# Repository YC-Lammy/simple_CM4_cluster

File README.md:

# simple_CM4_cluster
A simple compute module 4 cluster in a 120x120x60mm form-factor cabable of up to 7 pi.   

Each pi can work alone as a 78x58mm SBC.

Ports(per pi): 4 usb2.0, usb-c OTG, PCIE, 2 micro HDMI, CSI, DSI, micro SD and headers

The last six pin on the standard 40 way header has been removed on the board, include GPIO 16,19,20,21,26 and GND

SPI, I2C, UART are not affected, a standard HAT device can still be used.

The main board is powered by +12v through barrel jack or 4/8 pin PSU power. When the pi is alone, it could be powered through USB-A or pin headers

Two space left for EEPROM on the main PCB can be left open if custom program for the RTL8370 is not required. SW2 is a restart switch of RTL8370.

Requirement: kiCad version 5.99 or above

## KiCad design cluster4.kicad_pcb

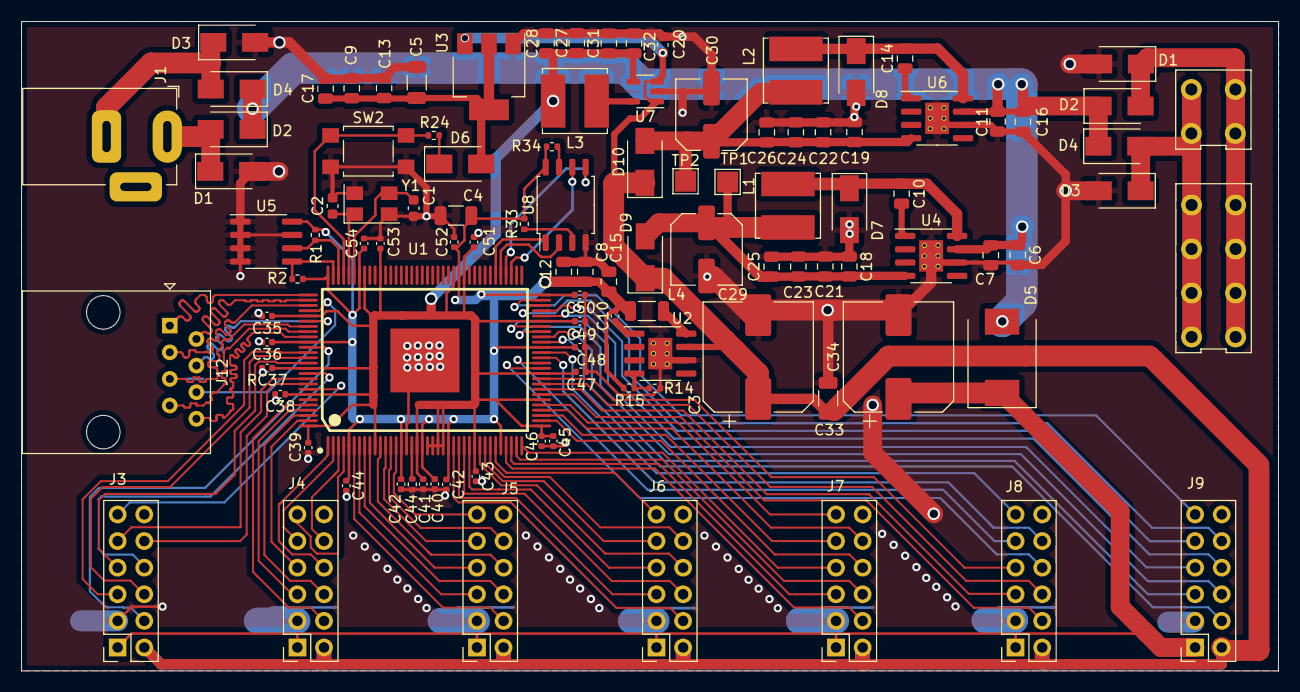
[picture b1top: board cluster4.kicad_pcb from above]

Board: 2 copper layers, 120.0 x 62.0 mm, 105 parts (0 on the bottom side), 93 nets.

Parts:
C1, C2: pf; C_0603_1608Metric
C3, C34: 470uf; CP_Elec_10x10
C4, C5: 100uf; C_1206_3216Metric
C6, C7, C11, C16, C18, C19, C21, C22, C23, C24, C25, C26: 10u; C_0805_2012Metric
C8, C9: 22uf; C_0805_2012Metric
C10: 10n; C_0402_1005Metric
C10#2, C14: 100n; C_0805_2012Metric
C12, C13, C15, C17, C27, C28, C31, C32: 10uf; C_0805_2012Metric
C20: 4.7uf; C_0603_1608Metric
C29, C30: 100uf; C_Elec_6.3x7.7
C33: 470uf; C_1206_3216Metric
C35, C36, C38, C39, C40, C41, C42, C42#2, C43, C44, C45, C46, C47, C48, C49, C50, C51, C52, C53, C54: 0.1uf; C_0402_1005Metric
C44#2: 2.49k; R_0402_1005Metric
D1, D1#2, D2, D2#2, D3, D3#2, D4, D4#2, D6, D9, D10: D; D_SMA
D5: D_SMC
D7, D8: 1n5824; D_SMA
J1: Barrel_Jack; BarrelJack_Horizontal
J2, J2#2: Conn_02x12_Top_Bottom; 5557_connector
J3, J4, J5, J6, J7, J8, J9: Conn_01x11_Female; PinSocket_2x06_P2.54mm_Vertical
J12: RJ45; RJ45_Amphenol_54602-x08_Horizontal
L1, L2: 22uh; L_Bourns_SRN6045TA
L3: 1uh; L_Bourns_SRN6045TA
L4: 6.8uh; L_1206_3216Metric
R1, R2, R15: 4.7k; R_0402_1005Metric
R14: 3k; R_0402_1005Metric
R24: 10k; R_0402_1005Metric
R33, R34: 1k; R_0402_1005Metric
RC37: 0.1uf; C_0402_1005Metric
SW2: SW_Push; SW_SPST_TL3305A
TP1, TP2: TestPoint; TestPoint_Pad_2.0x2.0mm
U1: RTL8370N; RTL8370
U2: LM22676-ADJ; SOIC-8-1EP_3.9x4.9mm_P1.27mm_EP2.29x3mm_ThermalVias
U3: AMS1117-3.3; SOT-223-3_TabPin2
U4, U6: LM22676-5.0; SOIC-8-1EP_3.9x4.9mm_P1.27mm_EP2.29x3mm_ThermalVias
U5: M24C02-FMN; SOIC-8_3.9x4.9mm_P1.27mm
U7: ADP2108AUJ-1.0; TSOT-23-5
U8: W25Q128JVS; SOIC-8_5.23x5.23mm_P1.27mm
Y1: 25Mhz; Crystal_SMD_5032-4Pin_5.0x3.2mm

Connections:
/+5v: C3.1, C20.1, C33.1, D9.1 (K), D10.1 (K), J3.2, J4.2, J5.2, J6.2, J7.2, J8.2, J9.2, U2.7, U3.3 (VI), U7.1 (Vin), U7.3 (EN)
/+12v: C34.1, D5.1, J3.1, J4.1, J5.1, J6.1, J7.1, J8.1, J9.1
/P0_AN: J12.2, U1.104 (P0MDIAN)
/P0_AP: J12.1, U1.103 (P0MDIAP)
/P0_BN: J12.6, U1.106 (P0MDIBN)
/P0_BP: J12.3, U1.105 (P0MDIBP)
/P0_CN: J12.5, U1.109 (P0MDICN)
/P0_CP: J12.4, U1.108 (P0MDICP)
/P0_DN: J12.8, U1.111 (P0MDIDN)
/P0_DP: J12.7, U1.110 (P0MDIDP)
/P1_AN: J3.5, U1.114 (P1MDIAN)
/P1_AP: J3.4, U1.113 (P1MDIAP)
/P1_BN: J3.7, U1.116 (P1MDIBN)
/P1_BP: J3.6, U1.115 (P1MDIBP)
/P1_CN: J3.9, U1.119 (P1MDICN)
/P1_CP: J3.8, U1.118 (P1MDICP)
/P1_DN: J3.11, U1.121 (P1MDIDN)
/P1_DP: J3.10, U1.120 (P1MDIDP)
/P2_AN: J4.5, U1.125 (P2MDIAN)
/P2_AP: J4.4, U1.124 (P2MDIAP)
/P2_BN: J4.7, U1.127 (P2MDIBN)
/P2_BP: J4.6, U1.126 (P2MDIBP)
/P2_CN: J4.9, U1.2 (P2MDICN)
/P2_CP: J4.8, U1.1 (P2MDICP)
/P2_DN: J4.11, U1.4 (P2MDIDN)
/P2_DP: J4.10, U1.3 (P2MDIDP)
/P3_AN: J5.5, U1.7 (P3MDIAN)
/P3_AP: J5.4, U1.6 (P3MDIAP)
/P3_BN: J5.7, U1.9 (P3MDIBN)
/P3_BP: J5.6, U1.8 (P3MDIBP)
/P3_CN: J5.9, U1.12 (P3MDICN)
/P3_CP: J5.8, U1.11 (P3MDICP)
/P3_DN: J5.11, U1.14 (P3MDIDN)
/P3_DP: J5.10, U1.13 (P3MDIDP)
/P4_AN: J6.5, U1.26 (P4MDIAN)
/P4_AP: J6.4, U1.25 (P4MDIAP)
/P4_BN: J6.7, U1.28 (P4MDIBN)
/P4_BP: J6.6, U1.27 (P4MDIBP)
/P4_CN: J6.9, U1.31 (P4MDICN)
/P4_CP: J6.8, U1.30 (P4MDICP)
/P4_DN: J6.11, U1.33 (P4MDIDN)
/P4_DP: J6.10, U1.32 (P4MDIDP)
/P5_AN: J7.5, U1.36 (P5MDIAN)
/P5_AP: J7.4, U1.35 (P5MDIAP)
/P5_BN: J7.7, U1.38 (P5MDIBN)
/P5_BP: J7.6, U1.37 (P5MDIBP)
/P5_CN: J7.9, U1.41 (P5MDICN)
/P5_CP: J7.8, U1.40 (P5MDICP)
/P5_DN: J7.11, U1.43 (P5MDIDN)
/P5_DP: J7.10, U1.42 (P5MDIDP)
/P6_AN: J8.5, U1.46 (P6MDIAN)
/P6_AP: J8.4, U1.45 (P6MDIAP)
/P6_BN: J8.7, U1.48 (P6MDIBN)
/P6_BP: J8.6, U1.47 (P6MDIBP)
/P6_CN: J8.9, U1.51 (P6MDICN)
/P6_CP: J8.8, U1.50 (P6MDICP)
/P6_DN: J8.11, U1.53 (P6MDIDN)
/P6_DP: J8.10, U1.52 (P6MDIDP)
/P7_AN: J9.5, U1.56 (P7MDIAN)
/P7_AP: J9.4, U1.55 (P7MDIAP)
/P7_BN: J9.7, U1.58 (P7MDIBN)
/P7_BP: J9.6, U1.57 (P7MDIBP)
/P7_CN: J9.9, U1.61 (P7MDICN)
/P7_CP: J9.8, U1.60 (P7MDICP)
/P7_DN: J9.11, U1.63 (P7MDIDN)
/P7_DP: J9.10, U1.62 (P7MDIDP)
/switch/+1v: C27.1, C28.1, C31.1, C32.1, C35.1, C38.1, C39.1, C41.1, C43.1, C45.1, C46.1, C47.1, C49.1, C51.1, C53.1, L3.2, RC37.1, U1.10 (AVDDL), U1.18 (AVDDL), U1.20 (DVDDL), U1.21 (DVDDL), U1.22 (DVDDL), U1.23 (DVDDL), U1.29 (AVDDL), U1.39 (AVDDL), U1.44 (PLLVDDL1), U1.49 (AVDDL), U1.59 (AVDDL), U1.76 (DVDDL), U1.78 (DVDDL), U1.92 (DVDDL), U1.95 (DVDDL), U1.107 (AVDDL), U1.117 (AVDDL), U1.122 (PLLVDDL0), U1.128 (AVDDL), U7.4 (FB)
/switch/SCK: R1.1, U1.100 (SCK/MDC), U5.6 (SCL)
/switch/SDA: R2.1, U1.101 (SDA/MDIO), U5.5 (SDA)
/switch/SPI_CLK: U1.67 (P7LED2), U8.6 (CLK)
/switch/SPI_CS: U1.70 (P6LED2), U8.1 (~CS)
/switch/SPI_D0: U1.69 (P7LED1), U8.2 (DO(IO1))
/switch/SPI_D1: U1.68 (P7LED0), U8.5 (DI(IO0))
/switch/nRESET: R24.2, SW2.1, U1.99 (nRESET)
<NO NET>: C4.1, C8.1, C10.2, C12.1, C15.1, C36.1, C40.1, C42.1, C42#2.1, C44.1, C48.1, C50.1, C52.1, C54.1, L4.1, R1.2, R2.2, R15.1, R33.2, R34.2, U1.5 (AVDDH), U1.15 (AVDDH), U1.19 (AVDDH), U1.24 (AVDDH), U1.34 (AVDDH), U1.54 (AVDDH), U1.64 (AVDDH), U1.77 (DVDDIO), U1.96 (AVDDH), U1.102 (AVDDH), U1.112 (AVDDH), U5.8 (VCC), U8.8 (VCC)
GND: C1.2, C2.2, C3.2, C4.2, C5.2, C6.2, C7.2, C8.2, C9.2, C11.2, C12.2, C13.2, C15.2, C16.2, C17.2, C18.2, C19.2, C20.2, C21.2, C22.2, C23.2, C24.2, C25.2, C26.2, C27.2, C28.2, C29.2, C30.2, C31.2, C32.2, C33.2, C34.2, C35.2, C36.2, C38.2, C39.2, C40.2, C41.2, C42.2, C42#2.2, C43.2, C44.2, C44#2.1, C45.2, C46.2, C47.2, C48.2, C49.2, C50.2, C51.2, C52.2, C53.2, C54.2, D1.2 (A), D1#2.2 (A), D3.2 (A), D3#2.2 (A), D7.2 (A), D8.2 (A), J3.3, J4.3, J5.3, J6.3, J7.3, J8.3, J9.3, R14.2, RC37.2, SW2.2, U1.16 (AGND), U1.129, U2.6, U2.9, U3.1 (GND), U4.6, U4.9, U5.1 (E0), U5.2 (E1), U5.3 (E2), U5.4 (VSS), U5.7 (~WC), U6.6, U6.9, U7.2 (GND), U8.4 (GND), Y1.2, Y1.4
unnamed: C1.1, U1.97 (XTAL0), Y1.3
unnamed: C2.1, U1.98 (XTAL1), Y1.1
unnamed: C6.1, C7.1, C11.1, C16.1, D2.1 (K), D2#2.1 (K), D4.1 (K), D4#2.1 (K), D5.2, U4.7, U6.7
unnamed: C5.1, C9.1, C13.1, C17.1, D6.2 (A), U3.2 (VO)
unnamed: C18.1, C21.1, C23.1, C25.1, C29.1, D9.2 (A), L1.2, TP1.1, U4.4 (FB)
unnamed: C19.1, C22.1, C24.1, C26.1, C30.1, D10.2 (A), L2.2, TP2.1, U6.4 (FB)
unnamed: D1#2.1 (K), D2#2.2 (A), J1.1
unnamed: D3#2.1 (K), D4#2.2 (A), J1.2
unnamed: D6.1 (K), R24.1
unnamed: C10#2.1, D7.1 (K), L1.1, U4.8
unnamed: C14.2, D8.1 (K), L2.1, U6.8
unnamed: D1.1 (K), D2.2 (A), J2.1 (Pin_2), J2#2.1 (Pin_2)
unnamed: D3.1 (K), D4.2 (A), J2.2 (Pin_13), J2#2.2 (Pin_13)
unnamed: L3.1, U7.5 (SW)
unnamed: C44#2.2, U1.17 (MDIREF)
unnamed: R33.1, U8.3 (IO2)
unnamed: R34.1, U8.7 (IO3)

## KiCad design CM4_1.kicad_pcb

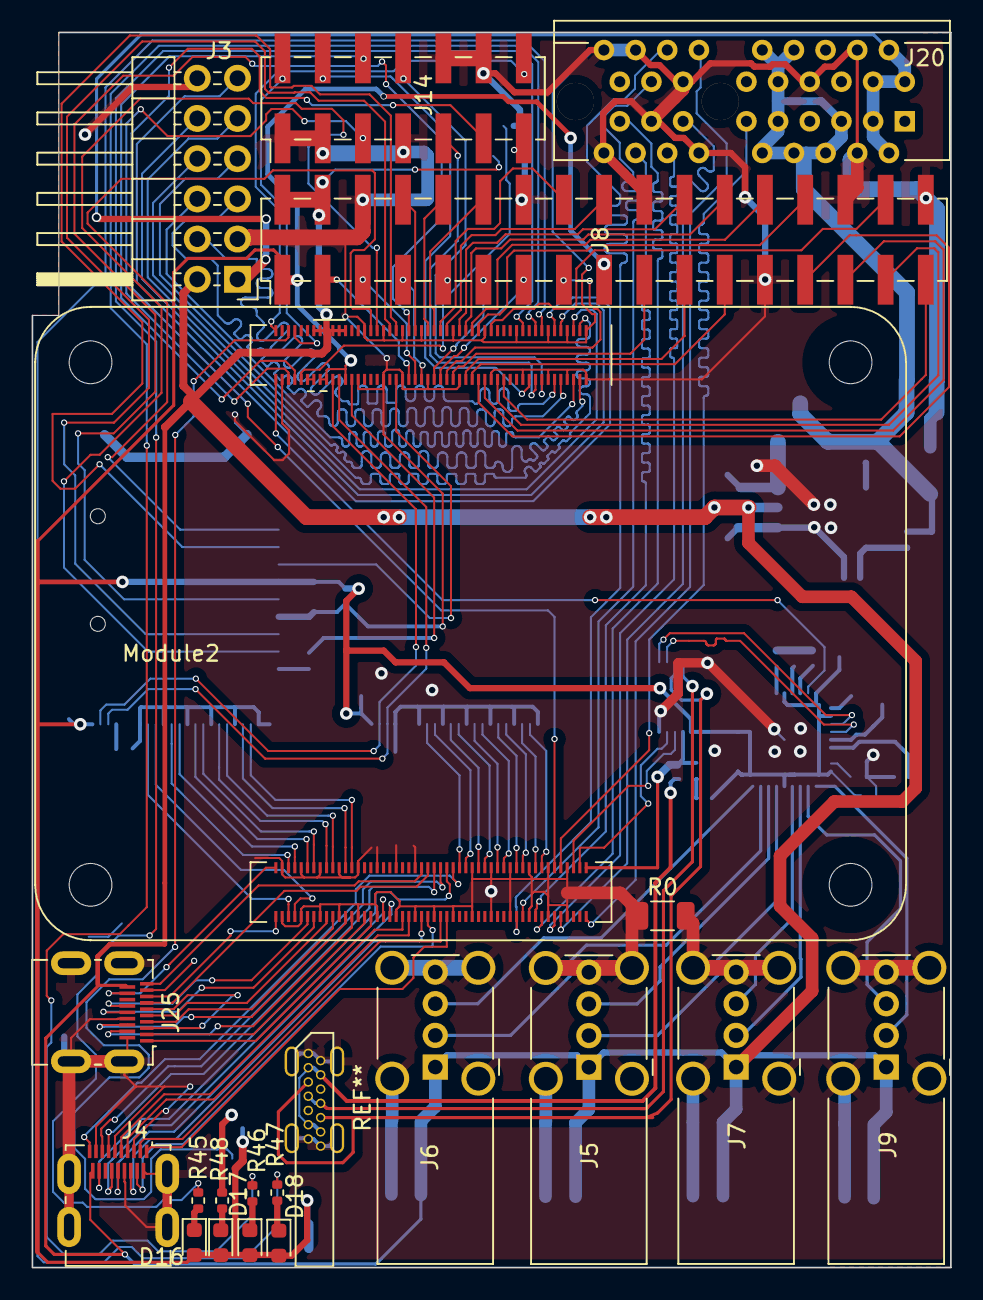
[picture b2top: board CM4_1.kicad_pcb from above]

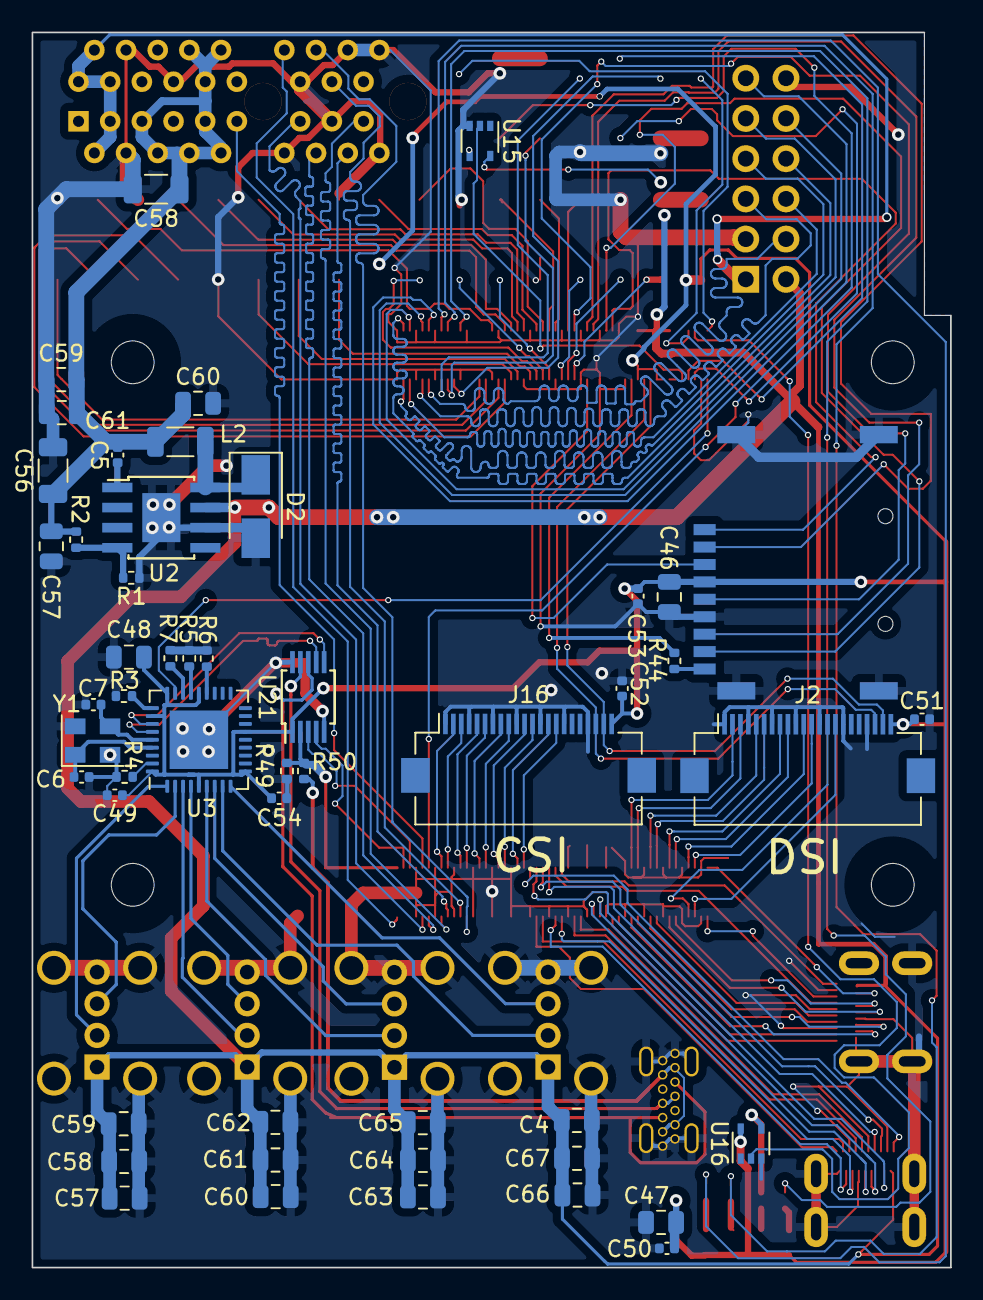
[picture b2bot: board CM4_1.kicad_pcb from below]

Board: 2 copper layers, 58.0 x 78.0 mm, 71 parts (51 on the bottom side), 142 nets.

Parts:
C4, C59, C62, C65: 22uf; C_0805_2012Metric
C5: 10nf; C_0402_1005Metric
C6, C7: 27pF; C_0402_1005Metric
C46, C47, C48, C57, C57#2, C58, C59#2, C60, C60#2, C61, C61#2, C63, C64, C66, C67: 10u; C_0805_2012Metric
C49, C50, C51, C52, C53, C54: 100n; C_0402_1005Metric
C56, C58#2: 100uf; C_1206_3216Metric
D2: SS36; D_SMA
D16: LED Green; LED_0603_1608Metric
D17: LED yellow; LED_0603_1608Metric
D18: LED green; LED_0603_1608Metric
D20: LED Red; LED_0603_1608Metric
J2, J16: Conn_01x22_Female; Hirose_FH12-22S-0.5SH_1x22-1MP_P0.50mm_Horizontal
J3: Conn_01x10_Female; PinHeader_2x06_P2.54mm_Horizontal
J4, J25: 690-019-298-412; HDMI_Micro-D_Molex_46765-1x01
J5, J6, J7, J9: USB_A; USB_A_Wuerth_614004134726_Horizontal
J8: THD-20-R; PinHeader_2x17_P2.54mm_Vertical_SMD
J13: Micro_SD_Card_Det; SD_slot
J14: Conn_02x07_Odd_Even; PinHeader_2x07_P2.54mm_Vertical_SMD
J20: 10018783-11200TLF; PCIex1-36
L2: 6.8uh; L_1206_3216Metric
Module2: ComputeModule4; Raspberry-Pi-4-Compute-Module
R0: 0R; R_1206_3216Metric
R1: 3k; R_0402_1005Metric
R2: 4.7k; R_0402_1005Metric
R3, R5, R6, R7: 36K 1%; R_0402_1005Metric
R4: 12K 1%; R_0402_1005Metric
R44: nf; R_0402_1005Metric
R45, R48: 1k; R_0402_1005Metric
R46, R47: 470R; R_0402_1005Metric
R49, R50: 2.2K 1%; R_0402_1005Metric
U2: LM22676MR-ADJ; TI_SO-PowerPAD-8
U3: USB2514B-I/M2; QFN-36-1EP_6x6mm_P0.5mm_EP3.7x3.7mm
U15, U16: 74LVC1G07SE-7; SOT-353_SC-70-5
U21: FSUSB42MUX; MSOP-10_3x3mm_P0.5mm
Y1: 24MHz; Crystal_SMD_EuroQuartz_MT-4Pin_3.2x2.5mm

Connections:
/+1.8v: Module2.88 (+1.8v_(Output)), Module2.90 (+1.8v_(Output))
/+3.3v: C46.1, C47.1, C48.1, C49.1, C50.1, C51.1, C52.1, C53.1, C54.1, D16.2 (A), D17.2 (A), D18.2 (A), D20.2 (A), J2.22, J8.1, J8.17, J13.4 (VDD), J16.22, Module2.78 (GPIO_VREF(1.8v/3.3v_Input)), Module2.84 (+3.3v_(Output)), Module2.86 (+3.3v_(Output)), U3.5 (VDDA33), U3.10 (VDDA33), U3.15 (VDD33), U3.23 (VDD33), U3.27 (VBUS_DET), U3.29 (VDDA33), U3.36 (VDDA33), U16.5 (VCC), U21.1 (VCC)
/+5v: C4.1, C57#2.2, C58.2, C59.1, C60#2.2, C61.2, C62.1, C63.2, C64.2, C65.1, C66.2, C67.2, J3.2, J4.18 (+5V), J5.1 (VBUS), J6.1 (VBUS), J7.1 (VBUS), J8.2, J8.4, J9.1 (VBUS), J25.18 (+5V), Module2.77 (+5v_(Input)), Module2.79 (+5v_(Input)), Module2.81 (+5v_(Input)), Module2.83 (+5v_(Input)), Module2.85 (+5v_(Input)), Module2.87 (+5v_(Input)), U2.7 (VIN), U15.5 (VCC)
/+12v: J3.1, J20.A2 (+12V), J20.A3 (+12V), J20.B1 (+12v), J20.B2 (+12v), J20.B3 (+12v)
/AIN0: J14.5, Module2.96 (AnalogIP0)
/AIN1: J14.6, Module2.94 (AnalogIP1)
/CAM1_C_N: J16.8, Module2.127 (CAM1_C_N)
/CAM1_C_P: J16.9, Module2.129 (CAM1_C_P)
/CAM1_D0_N: J16.2, Module2.115 (CAM1_D0_N)
/CAM1_D0_P: J16.3, Module2.117 (CAM1_D0_P)
/CAM1_D1_N: J16.5, Module2.121 (CAM1_D1_N)
/CAM1_D1_P: J16.6, Module2.123 (CAM1_D1_P)
/CAM1_D2_N: J16.11, Module2.133 (CAM1_D2_N)
/CAM1_D2_P: J16.12, Module2.135 (CAM1_D2_P)
/CAM1_D3_N: J16.14, Module2.139 (CAM1_D3_N)
/CAM1_D3_P: J16.15, Module2.141 (CAM1_D3_P)
/DSI1_C_N: J2.8, Module2.187 (DSI1_C_N)
/DSI1_C_P: J2.9, Module2.189 (DSI1_C_P)
/DSI1_D0_N: J2.2, Module2.175 (DSI1_D0_N)
/DSI1_D0_P: J2.3, Module2.177 (DSI1_D0_P)
/DSI1_D1_N: J2.5, Module2.181 (DSI1_D1_N)
/DSI1_D1_P: J2.6, Module2.183 (DSI1_D1_P)
/DSI1_D2_N: J2.11, Module2.193 (DSI1_D2_N)
/DSI1_D2_P: J2.12, Module2.195 (DSI1_D2_P)
/DSI1_D3_N: J2.14, Module2.194 (DSI1_D3_N)
/DSI1_D3_P: J2.15, Module2.196 (DSI1_D3_P)
/EEPROM_nWP: J14.4, Module2.20 (EEPROM_nWP)
/ETH_LEDG: Module2.15 (Ethernet_nLED3(3.3v)), R47.2
/ETH_LEDY: Module2.17 (Ethernet_nLED2(3.3v)), R46.2
/GLOBAL_EN: J14.14, Module2.99 (Global_EN)
/GPIO2: J8.3, Module2.58 (GPIO2)
/GPIO3: J8.5, Module2.56 (GPIO3)
/GPIO4: J8.7, Module2.54 (GPIO4)
/GPIO5: J8.29, Module2.34 (GPIO5)
/GPIO6: J8.31, Module2.30 (GPIO6)
/GPIO7: J8.26, Module2.37 (GPIO7)
/GPIO8: J8.24, Module2.39 (GPIO8)
/GPIO9: J8.21, Module2.40 (GPIO9)
/GPIO10: J8.19, Module2.44 (GPIO10)
/GPIO11: J8.23, Module2.38 (GPIO11)
/GPIO12: J8.32, Module2.31 (GPIO12)
/GPIO13: J8.33, Module2.28 (GPIO13)
/GPIO14: J8.8, Module2.55 (GPIO14)
/GPIO15: J8.10, Module2.51 (GPIO15)
/GPIO17: J8.11, Module2.50 (GPIO17)
/GPIO18: J8.12, Module2.49 (GPIO18)
/GPIO22: J8.15, Module2.46 (GPIO22)
/GPIO23: J8.16, Module2.47 (GPIO23)
/GPIO24: J8.18, Module2.45 (GPIO24)
/GPIO25: J8.22, Module2.41 (GPIO25)
/GPIO27: J8.13, Module2.48 (GPIO27)
/HD1_N: J9.2 (D-), U3.1 (USBDM_DN1/PRT_DIS_M1)
/HD1_P: J9.3 (D+), U3.2 (USBDP_DN1/PRT_DIS_P1)
/HD2_N: J7.2 (D-), U3.3 (USBDM_DN2/PRT_DIS_M2)
/HD2_P: J7.3 (D+), U3.4 (USBDP_DN2/PRT_DIS_P2)
/HD3_N: J5.2 (D-), U3.6 (USBDM_DN3/PRT_DIS_M3)
/HD3_P: J5.3 (D+), U3.7 (USBDP_DN3/PRT_DIS_P3)
/HD4_N: J6.2 (D-), U3.8 (USBDM_DN4/PRT_DIS_M4)
/HD4_P: J6.3 (D+), U3.9 (USBDP_DN4/PRT_DIS_P4)
/HDMI0_CEC: J25.13 (CEC), Module2.151 (HDMI0_CEC)
/HDMI0_CK_N: J25.12 (CK-), Module2.190 (HDMI0_CLK_N)
/HDMI0_CK_P: J25.10 (CK+), Module2.188 (HDMI0_CLK_P)
/HDMI0_D0_N: J25.9 (D0-), Module2.184 (HDMI0_TX0_N)
/HDMI0_D0_P: J25.7 (D0+), Module2.182 (HDMI0_TX0_P)
/HDMI0_D1_N: J25.6 (D1-), Module2.178 (HDMI0_TX1_N)
/HDMI0_D1_P: J25.4 (D1+), Module2.176 (HDMI0_TX1_P)
/HDMI0_D2_N: J25.3 (D2-), Module2.172 (HDMI0_TX2_N)
/HDMI0_D2_P: J25.1 (D2+), Module2.170 (HDMI0_TX2_P)
/HDMI0_HOTPLUG: J25.19 (HPD/HEAC-), Module2.153 (HDMI0_HOTPLUG)
/HDMI0_SCL: J25.15 (SCL), Module2.200 (HDMI0_SCL)
/HDMI0_SDA: J25.16 (SDA), Module2.199 (HDMI0_SDA)
/HDMI1_CEC: J4.13 (CEC), Module2.149 (HDMI1_CEC)
/HDMI1_CK_N: J4.12 (CK-), Module2.166 (HDMI1_CLK_N)
/HDMI1_CK_P: J4.10 (CK+), Module2.164 (HDMI1_CLK_P)
/HDMI1_D0_N: J4.9 (D0-), Module2.160 (HDMI1_TX0_N)
/HDMI1_D0_P: J4.7 (D0+), Module2.158 (HDMI1_TX0_P)
/HDMI1_D1_N: J4.6 (D1-), Module2.154 (HDMI1_TX1_N)
/HDMI1_D1_P: J4.4 (D1+), Module2.152 (HDMI1_TX1_P)
/HDMI1_D2_N: J4.3 (D2-), Module2.148 (HDMI1_TX2_N)
/HDMI1_D2_P: J4.1 (D2+), Module2.146 (HDMI1_TX2_P)
/HDMI1_HOTPLUG: J4.19 (HPD/HEAC-), Module2.143 (HDMI1_HOTPLUG)
/HDMI1_SCL: J4.15 (SCL), Module2.147 (HDMI1_SCL)
/HDMI1_SDA: J4.16 (SDA), Module2.145 (HDMI1_SDA)
/ID_SC: J8.28, Module2.35 (ID_SC)
/ID_SD: J8.27, Module2.36 (ID_SD)
/PCIE_CLK_N: J20.A14 (REFCLK-), Module2.112 (PCIe_CLK_N)
/PCIE_CLK_P: J20.A13 (REFCLK+), Module2.110 (PCIe_CLK_P)
/PCIE_CLK_nREQ: J20.B12 (nCLKREQ), Module2.102 (PCIe_CLK_nREQ)
/PCIE_RX_N: J20.A16 (PERP0), Module2.118 (PCIe_RX_N)
/PCIE_RX_P: J20.A17 (PERN0), Module2.116 (PCIe_RX_P)
/PCIE_TX_N: J20.B14 (PETP0), Module2.124 (PCIe_TX_N)
/PCIE_TX_P: J20.B15 (PETN0), Module2.122 (PCIe_TX_P)
/PCIE_nRST: J20.A11 (nPERST), Module2.109 (PCIe_nRST)
/RUN_PG: Module2.92 (RUN_PG), U15.2
/SCL0: J2.20, J16.20, Module2.80 (SCL0)
/SDA0: J2.21, J16.21, Module2.82 (SDA0)
/SD_CLK: J13.5 (CLK), Module2.57 (SD_CLK)
/SD_CMD: J13.3 (CMD), Module2.62 (SD_CMD)
/SD_DAT0: J13.7 (DAT0), Module2.63 (SD_DAT0)
/SD_DAT1: J13.8 (DAT1), Module2.67 (SD_DAT1)
/SD_DAT2: J13.1 (DAT2), Module2.69 (SD_DAT2)
/SD_DAT3: J13.2 (DAT3/CD), Module2.61 (SD_DAT3)
/SD_DET: Module2.76 (Reserved), R44.1
/SYNC_IN: J14.8, Module2.16 (Ethernet_SYNC_IN(1.8v))
/SYNC_OUT: J14.9, Module2.18 (Ethernet_SYNC_OUT(1.8v))
/TRD0_N: J3.5, Module2.10 (Ethernet_Pair0_N)
/TRD0_P: J3.4, Module2.12 (Ethernet_Pair0_P)
/TRD1_N: J3.6, Module2.6 (Ethernet_Pair1_N)
/TRD1_P: J3.7, Module2.4 (Ethernet_Pair1_P)
/TRD2_N: J3.10, Module2.9 (Ethernet_Pair2_N)
/TRD2_P: J3.11, Module2.11 (Ethernet_Pair2_P)
/TRD3_N: J3.9, Module2.5 (Ethernet_Pair3_N)
/TRD3_P: J3.8, Module2.3 (Ethernet_Pair3_P)
/TV_OUT: J14.11, Module2.111 (VDAC_COMP)
/USB2_N: Module2.103 (USB2_N), U21.4 (D_N)
/USB2_P: Module2.105 (USB2_P), U21.3 (D_P)
/USBH_N: U3.30 (USBDM_UP), U21.6 (HSD0_M)
/USBH_P: U3.31 (USBDP_UP), U21.7 (HSD0_P)
/USBOTG: Module2.101 (USB_OTG_ID), R49.1, R50.2, U21.2 (SEL)
/nEXTRST: Module2.100 (nEXTRST), U3.26 (RESET_N)
/nPWR_LED: Module2.95 (nPI_LED_PWR), U16.2
/nRPIBOOT: J14.2, Module2.93 (nRPIBOOT)
/pcie+3.3v: C5.2, C56.1, C57.1, C58#2.1, C59#2.1, C60.1, C61#2.1, J20.A5 (TCK), J20.A6 (TDI), J20.A8 (TMS), J20.A9 (+3.3V), J20.A10 (+3.3V), J20.B8 (+3.3v), J20.B9 (nTRST), J20.B10 (+3.3vAUX), L2.2, R2.1
GND: C4.2, C6.2, C7.2, C46.2, C47.2, C48.2, C49.2, C50.2, C51.2, C52.2, C53.2, C54.2, C56.2, C57.2, C57#2.1, C58.1, C58#2.2, C59.2, C59#2.2, C60.2, C60#2.1, C61.1, C61#2.2, C62.2, C63.1, C64.1, C65.2, C66.1, C67.1, D2.2 (A), J2.1, J2.4, J2.7, J2.10, J2.13, J2.16, J2.19, J3.3, J3.12, J4.2 (D2S), J4.5 (D1S), J4.8 (D0S), J4.11 (CKS), J4.17 (GND), J4.SH, J5.4 (GND), J5.5 (Shield), J6.4 (GND), J6.5 (Shield), J7.4 (GND), J7.5 (Shield), J8.6, J8.9, J8.14, J8.20, J8.25, J8.30, J8.34, J9.4 (GND), J9.5 (Shield), J13.6 (VSS), J13.11 (SHIELD), J14.1, J14.3, J14.7, J14.10, J14.12, J16.1, J16.4, J16.7, J16.10, J16.13, J16.16, J16.19, J20.A4 (GND), J20.A12 (GND), J20.A15 (GND), J20.A18 (GND), J20.B4 (GND), J20.B7 (GND), J20.B13 (GND), J20.B16 (GND), J20.B18 (GND), J25.2 (D2S), J25.5 (D1S), J25.8 (D0S), J25.11 (CKS), J25.17 (GND), J25.SH, Module2.1 (GND), Module2.2 (GND), Module2.7 (GND), Module2.8 (GND), Module2.13 (GND), Module2.14 (GND), Module2.22 (GND), Module2.23 (GND), Module2.32 (GND), Module2.33 (GND), Module2.42 (GND), Module2.43 (GND), Module2.52 (GND), Module2.53 (GND), Module2.59 (GND), Module2.60 (GND), Module2.65 (GND), Module2.66 (GND), Module2.71 (GND), Module2.74 (GND), Module2.98 (GND), Module2.107 (GND), Module2.108 (GND), Module2.113 (GND), Module2.114 (GND), Module2.119 (GND), Module2.120 (GND), Module2.125 (GND), Module2.126 (GND), Module2.131 (GND), Module2.132 (GND), Module2.137 (GND), Module2.138 (GND), Module2.144 (GND), Module2.150 (GND), Module2.155 (GND), Module2.156 (GND), Module2.161 (GND), Module2.162 (GND), Module2.167 (GND), Module2.168 (GND), Module2.173 (GND), Module2.174 (GND), Module2.179 (GND), Module2.180 (GND), Module2.185 (GND), Module2.186 (GND), Module2.191 (GND), Module2.192 (GND), Module2.197 (GND), Module2.198 (GND), R0.1, R0.2, R1.1, R3.2, R4.1, R5.2, R6.2, R7.2, R49.2, U2.6 (GND), U2.9 (EP), U3.37 (VSS), U15.3 (GND), U16.3 (GND), U21.5 (GND), U21.10 (nOE), Y1.2, Y1.4
unnamed: C5.1, U2.1 (BOOT)
unnamed: C6.1, U3.33 (XTALIN/CLKIN), Y1.1
unnamed: C7.1, U3.32 (XTALOUT), Y1.3 (2)
unnamed: D2.1 (K), L2.1, U2.8 (SW)
unnamed: D16.1 (K), R45.2
unnamed: D17.1 (K), R46.1
unnamed: D18.1 (K), R47.1
unnamed: D20.1 (K), R48.1
unnamed: J13.9 (DET_B), R44.2
unnamed: J14.13, U15.4
unnamed: Module2.21 (PI_nLED_Activity), R45.1
unnamed: R1.2, R2.2, U2.4 (FB)
unnamed: R3.1, U3.28 (SUSP_IND/LOCAL_PWR/NON_REM0)
unnamed: R4.2, U3.35 (RBIAS)
unnamed: R5.1, U3.24 (SCL/SMBCLK/CFG_SEL0)
unnamed: R6.1, U3.22 (SDA/SMBDATA/NON_REM1)
unnamed: R7.1, U3.25 (HS_IND/CFG_SEL1)
unnamed: R48.2, U16.4

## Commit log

2021-01-28 Update LICENSE
